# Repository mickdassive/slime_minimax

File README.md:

# slime_minimax
hardware project based on slime vr full body trackers. im still working on adding support for aditonal chips. 
# hardware
as of right now the bno085 is confirmed working irl.
however im working on adding support for all other supported IMUs

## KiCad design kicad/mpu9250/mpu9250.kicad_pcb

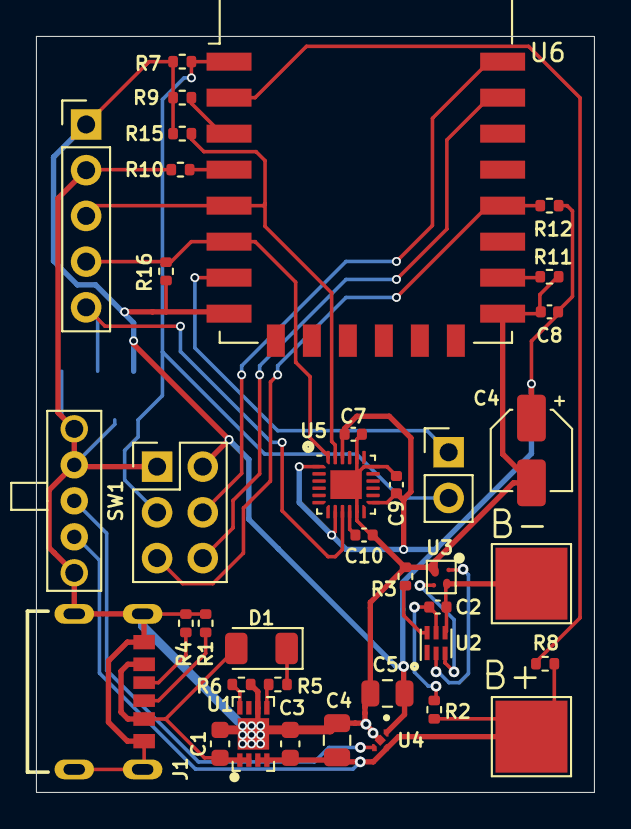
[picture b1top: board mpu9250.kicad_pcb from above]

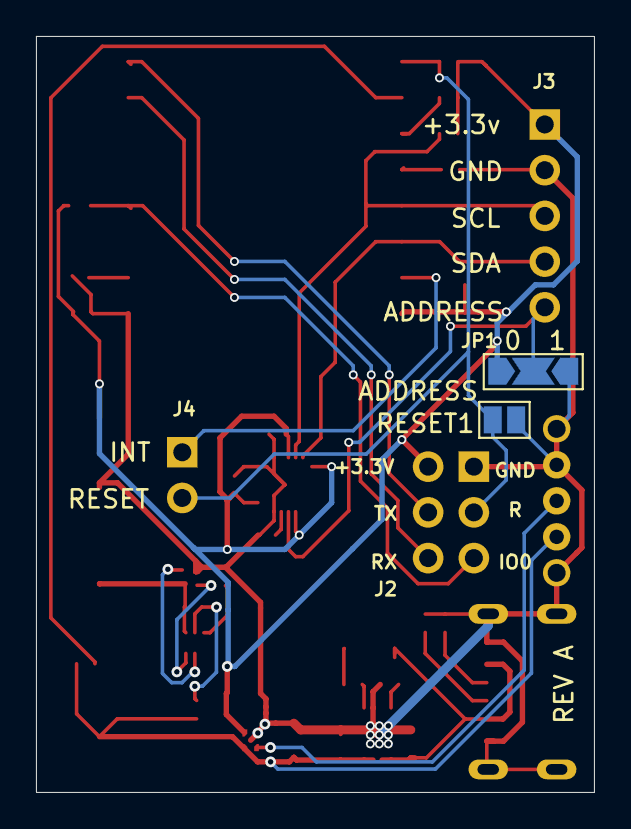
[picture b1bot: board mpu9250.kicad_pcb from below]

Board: 2 copper layers, 31.0 x 42.0 mm, 40 parts (2 on the bottom side), 26 nets.

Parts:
B+: TestPoint_Pad_4.0x4.0mm
B-: TestPoint_Pad_4.0x4.0mm
C1, C3: 4.7uf; C_0603_1608Metric
C2, C7, C8, C9, C10: 100nf; C_0402_1005Metric
C4: 1uf; CP_Elec_4x4.5
C4#2, C5: 1uf; C_0805_2012Metric
D1: c-stat; D_1206_3216Metric
J1: USB4125-GF-A_REVA; GCT_USB4125-GF-A_REVA
J2: PinHeader_2x03_P2.54mm_Vertical
J3: PinHeader_1x05_P2.54mm_Vertical
J4: PinHeader_1x02_P2.54mm_Vertical
JP1: SolderJumper-3_P2.0mm_Open_TrianglePad1.0x1.5mm
R1, R4: 5.1k; R_0402_1005Metric
R2: 330; R_0402_1005Metric
R3, R15, R16: 2.2k; R_0402_1005Metric
R5: 470; R_0402_1005Metric
R6: 2k; R_0402_1005Metric
R7, R9, R10, R11, R12: 10k; R_0402_1005Metric
R8: 180k; R_0402_1005Metric
RESET1: SolderJumper-2_P1.3mm_Open_Pad1.0x1.5mm
SW1: SW_SPDT; A107673
U1: dfn-8_wide
U2: BQ297xy; WSON-6_1.5x1.5mm_P0.5mm
U3: CSD85302L; 4-XFLGA
U4: NCP177BMX330TCG; VREG_NCP170AMX300TCG
U5: mpu9250; QFN-24-1EP_3x3mm_P0.4mm_EP1.75x1.6mm
U6: ESP-12E

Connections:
+3.3V: C4.1, C5.1, C7.2, C8.2, C9.2, J2.2, J3.1, JP1.3, R7.1, R9.1, R12.1, R15.2, R16.2, U4.1 (OUT), U5.1 (RESV), U5.8 (VDDIO), U5.13 (VDD), U5.22 (nCS), U6.8
+5V: C1.1, D1.2 (A), J1.A9 (VBUS), J1.B9 (VBUS), U1.1, U1.2
+BATT: B+.1, C3.2, C4#2.1, R2.2, R8.1, SW1.3 (C), U1.3, U1.4, U4.4 (IN)
-BATT: C2.1, U2.4 (VSS), U3.2 (S2)
/ADC: R8.2, U6.2
/ADDRESS: J3.5, JP1.2, U5.9 (AD0/SD0)
/BAT_SENCE: C2.2, R2.1, U2.5 (BAT)
/CC1: J1.A5 (CC1), R4.1
/CC2: J1.B5 (CC2), R1.1
/CH_STAT: R5.1, U1.5
/ESP_EN: R9.2, U6.3
/GPIO0: J2.5, R12.2, U6.18
/GPIO15: R11.1, U6.16
/G_C: U2.2 (Cout), U3.1 (G1)
/G_D: U2.3 (Dout), U3.3 (G2)
/H_SCL: J3.3, R15.1, U5.23 (SCL/SCLK), U6.5
/H_SDA: J3.4, R16.1, U5.24 (SDA/SDI), U6.6
/INT: J4.1, U6.7
/REG_EN: SW1.2 (B), U4.3 (EN)
/RESET: J2.3, J4.2, R7.2, RESET1.2, U6.1
/RX: J2.6, U6.21
/TX: J2.4, U6.22
/V-: R3.2, U2.6 (V-)
GND: C1.2, C3.1, C4.2, C4#2.2, C5.2, C7.1, C8.1, C9.1, C10.1, J1.A12 (GND), J1.B12 (GND), J1.S1 (SHIELD), J1.S2 (SHIELD), J1.S3 (SHIELD), J1.S4 (SHIELD), J2.1, J3.2, JP1.1, R1.2, R3.1, R4.2, R6.1, R10.2, R11.2, RESET1.1, SW1.1 (A), SW1.4, SW1.5, U1.6, U1.9, U3.4 (S1), U4.2 (GND), U4.5, U5.11 (FSYNC), U5.18 (GND), U5.20 (RESV), U5.25, U6.15
unnamed: C10.2, U5.10 (REGOUT)
unnamed: D1.1 (K), R5.2

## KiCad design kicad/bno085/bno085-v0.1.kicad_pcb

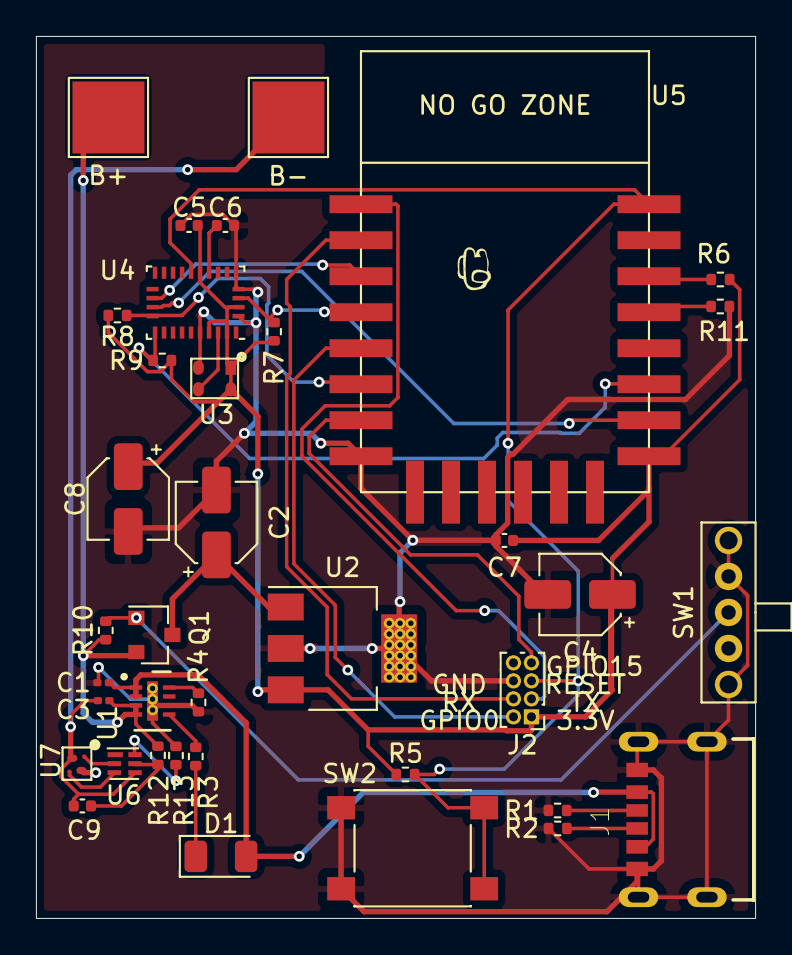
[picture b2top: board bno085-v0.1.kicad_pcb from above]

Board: 2 copper layers, 40.0 x 49.0 mm, 37 parts (0 on the bottom side), 30 nets.

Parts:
B+: TestPoint_Pad_4.0x4.0mm
B-: TestPoint_Pad_4.0x4.0mm
C1, C3: 4.7uf; C_0201_0603Metric
C2, C4, C8: 1uf; CP_Elec_4x4.5
C5, C6, C7, C9: 100nf; C_0402_1005Metric
D1: c-stat; D_1206_3216Metric
J1: USB4125-GF-A_REVA; GCT_USB4125-GF-A_REVA
J2: esp program; PinHeader_2x04_P1.00mm_Vertical
Q1: SSM3J372R; SOT-23
R1, R2: 5.1k; R_0402_1005Metric
R3: 470; R_0402_1005Metric
R4: 2k; R_0402_1005Metric
R5, R6, R10, R11: 10k; R_0402_1005Metric
R7, R8, R9, R13: 2.2k; R_0402_1005Metric
R12: 330; R_0402_1005Metric
SW1: SW_SPDT; A107673
SW2: SW_MEC_5E; SW_Push_1P1T_NO_6x6mm_H9.5mm
U1: MCP73832-2-OT; DFN-8-1EP_2x3mm_P0.5mm_EP0.61x2.2mm
U2: TC1108-3.3; SOT-223-3_TabPin2
U3: KC2016 @ 32.768MHZ; kc2016
U4: BNO085; LGA-28_5.2x3.8mm_P0.5mm
U5: ESP-12F; esp-12f
U6: BQ297xy; WSON-6_1.5x1.5mm_P0.5mm
U7: CSD85302L; 4-XFLGA

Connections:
3.3v: C4.1, C5.1, C7.2, C8.1, J2.1, R5.1, R6.1, R7.1, R8.2, R9.2, U2.3, U3.1, U3.4, U4.3, U4.10, U4.26, U4.28, U5.8
5v: C1.1, D1.2, J1.A9, J1.B9, U1.1, U1.2
B+: B+.1, C3.2, Q1.2, R10.2, R12.2, U1.3, U1.4
B-: B-.1, C3.1, C9.1, U6.4, U7.2
BOOTN: R7.2, U4.4, U5.19
CH_PROG: R4.2, U1.8
CH_STAT: R3.1, U1.5
CS: U4.18, U5.7
GND: C1.2, C2.2, C4.2, C5.2, C6.2, C7.1, C8.2, J1.A12, J1.B12, J1.S1, J1.S2, J1.S3, J1.S4, J2.6, R1.2, R2.2, R4.1, R11.2, R13.1, SW1.3, SW1.4, SW1.5, SW2.1, SW2.2, U1.6, U1.9, U2.2, U3.2, U4.2, U4.5, U4.6, U4.25, U5.15, U7.4
GPIO0: J2.2, U5.18
GPIO15: J2.7, U5.16
H_SCL: R8.1, U4.19, U5.17
H_SDA: R9.1, U4.20, U5.6
MOSI: U4.17, U5.20
unnamed: C6.1, U4.9
unnamed: C9.2, R12.1, U6.5
unnamed: D1.1, R3.2
unnamed: J1.A5, R2.1
unnamed: J1.B5, R1.1
unnamed: R6.2, U5.3
unnamed: R11.1, U5.4
unnamed: R13.2, U6.6
unnamed: U3.3, U4.27
unnamed: U6.2, U7.1
unnamed: U6.3, U7.3
REG_IN: C2.1, Q1.3, U2.1
RESET: J2.5, R5.2, SW2.3, SW2.4, U4.11, U5.1
RX: J2.4, U5.21
SW1: Q1.1, R10.1, SW1.2
TX: J2.3, U5.22

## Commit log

2022-11-16 added kicad files
2022-11-16 updated titel block
2022-11-16 added git ignore
2022-11-16 changed naming conventions
2022-11-16 test
2022-11-16 testing
2022-11-16 setting things up for other chips
2022-11-17 added Datasheets and updated shimatics for bno085 board
2022-11-17 added basic support for bmi160, it shold work i haven had a chance to test thogh
2022-11-17 removed old/redundant files
2022-11-17 re-added missing LICENSE and .gitignore files
2022-11-17 added adional dicrectorys for all chips supperted by slimevr
2022-11-17 added addional datasheets
2022-11-17 changed foldr naming convention
2022-11-17 added bno055 support unfortunately some componts ha to be mouted on the back as they were to lage for the front
2022-11-17 removed useless files
2022-11-17 stated work on mpu9250 not finnished
2022-11-18 made minor cahnges to bno085 schimatic + pcb to better reflect the real world version
2022-11-18 remoing old files
2022-11-18 added support for mpu9250
2022-11-22 addded firmware working out bugs rn
2022-12-02 migrateing devopment to dev brantch
2022-12-02 migrateing to dev brantch
